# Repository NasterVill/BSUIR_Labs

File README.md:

# BSUIR (Belarusian State University of Informatics and Radioelectronics) laboratory works

## Intro
Here I've gathered most of the laboratory works from the CMSnN (Computing Machines, Systems and Networks) course which I've been working on. Some of the labs are far beyond redemption, but all the others are or will be here.

## Course Navigation

### 1 term

* [Algorithms and Programming Foundations](https://github.com/NasterVill/BSUIR_Labs/tree/master/1%20term/Algorithms-and-Programming-Foundations)

### 2 term

* [Algorithms and Programming Foundations](https://github.com/NasterVill/BSUIR_Labs/tree/master/2%20term/Algorithms-and-Programming-Foundations)
* [Arithmetic and Logic Basics of Computing Machines (Course Work)](https://github.com/NasterVill/BSUIR_Labs/tree/master/CourseWorks/Arithmetic-and-Logic-Basics-of-Computing-Machines)

### 3 term
* [Programming Design and Programming Languages (C++)](https://github.com/NasterVill/BSUIR_Labs/tree/master/3%20term/Programming-Design-and-Programming-Languages-C%2B%2B)
* [Lightning Paint (Course Work)](https://github.com/NasterVill/BSUIR_Labs/tree/master/CourseWorks/LightningPaint)
An application for drawing and simple image editing

### 4 term
* [System Software](https://github.com/NasterVill/BSUIR_Labs/tree/master/4%20term/System_Software_-SPO-)
* [Cross Platform Programming](https://github.com/NasterVill/BSUIR_Labs/tree/master/4%20term/Cross_Platform_Programming-Course)
* [Programming Design and Programming Languages (Assembly)](https://github.com/NasterVill/BSUIR_Labs/tree/master/4%20term/Programming-Design-and-Programming-Languages-Assembly)
* [Personal Computer Architecture](https://github.com/NasterVill/BSUIR_Labs/tree/master/4%20term/Personal-Computer-Architecture)
* [Lightning Tuner (Course Work)](https://github.com/NasterVill/BSUIR_Labs/tree/master/CourseWorks/LightningTuner)
An application for guitar tuning (written in Java) based of FFT algorithm

### 5 term

* [Interfaces and Peripheral Devices](https://github.com/NasterVill/BSUIR_Labs/tree/master/5%20term/Interfaces-and-Peripheral-Devices-IPD-)
* [Theoretical Foundations of Computer Networks](https://github.com/NasterVill/BSUIR_Labs/tree/master/5%20term/Theoretical-Foundations-of-Computer-Networks-TFoCN)
* [Structural and Functional Organization of Electronic Computing Machines](https://github.com/NasterVill/BSUIR_Labs/tree/master/5%20term/Structural-and-Functional-Organization-of-Electronic-%D0%A1omputing-Machines-SFOECM)
* [Circuit Design (Course Work)](https://github.com/NasterVill/BSUIR_Labs/tree/master/CourseWorks/Circuit-Design)

### 6 term

* [Digital Signal and Image Processing](https://github.com/NasterVill/BSUIR_Labs/tree/master/6%20term/DSIP-Digital-Signal-and-Image-Processing-)
* [System Analysis](https://github.com/NasterVill/BSUIR_Labs/tree/master/6%20term/SA%20(System-Analysis))
* [High Performance Processors Architecture](https://github.com/NasterVill/BSUIR_Labs/tree/master/6%20term/HPPA-High-Performance-Processors-Architecture)
* [Software Development and Testing Technologies](https://github.com/NasterVill/BSUIR_Labs/tree/master/6%20term/GoParty%20(Software-Development-and-Testing-Technologies))

### 7 term

* [Digital Signal and Image Processing](https://github.com/NasterVill/BSUIR_Labs/tree/master/7%20term/DSIP-Digital-Signal-and-Image-Processing)
* [Computer Aided Design of Computers and Systems](https://github.com/NasterVill/BSUIR_Labs/tree/master/7%20term/Computer-Aided-Design-of-Computers-and-Systems)
* [Local Computer Networks System Software](https://github.com/NasterVill/BSUIR_Labs/tree/master/7%20term/Local-Computer-Networks-System-Software)
* [Microprocessor Systems and Tools](https://github.com/NasterVill/BSUIR_Labs/tree/master/7%20term/Microprocessor-Systems-and-Tools)
* [Modeling](https://github.com/NasterVill/BSUIR_Labs/tree/master/7%20term/Modeling)

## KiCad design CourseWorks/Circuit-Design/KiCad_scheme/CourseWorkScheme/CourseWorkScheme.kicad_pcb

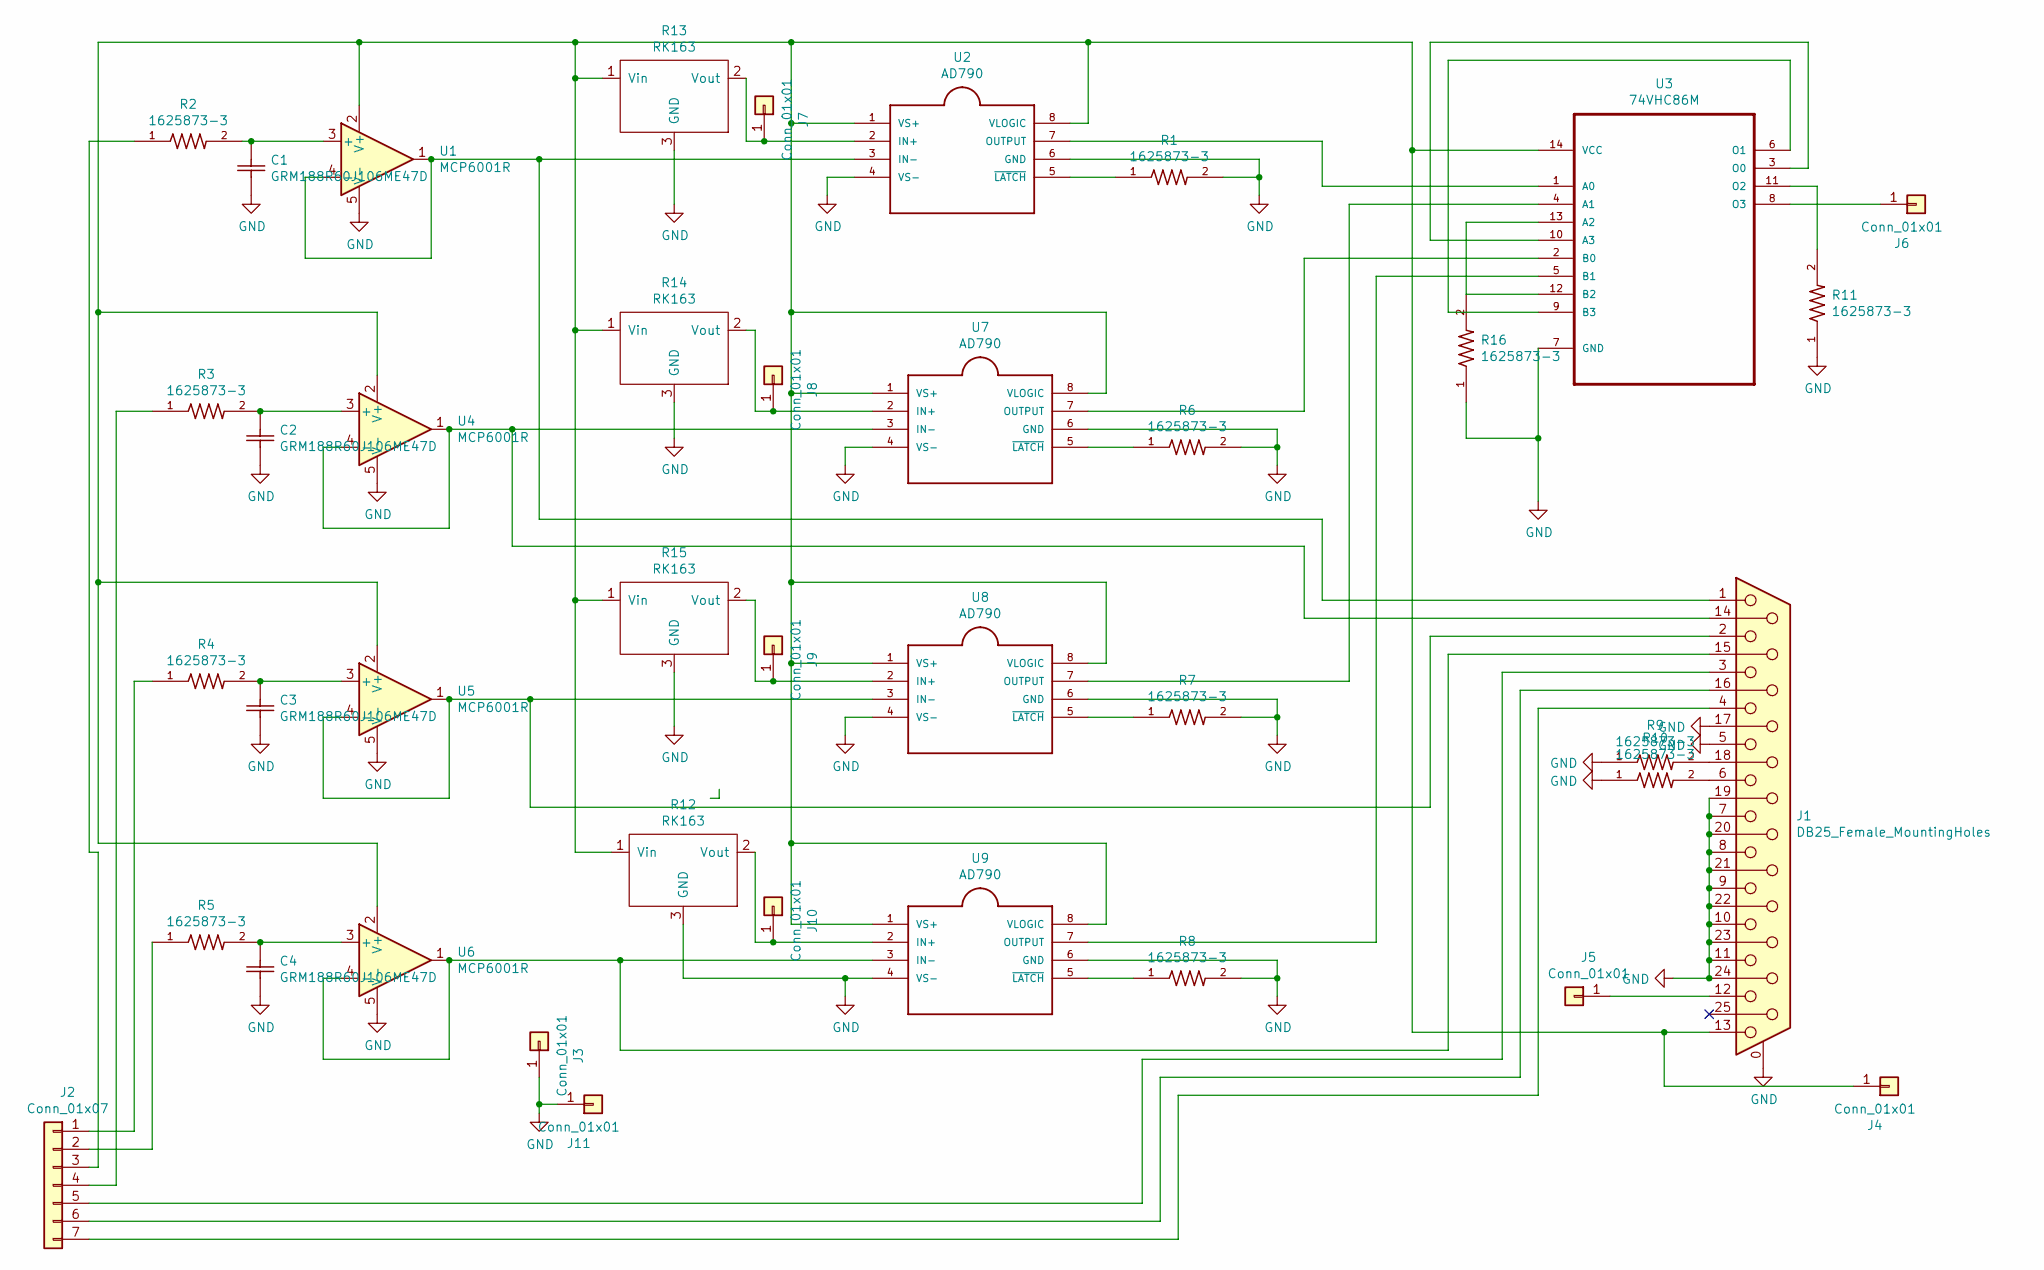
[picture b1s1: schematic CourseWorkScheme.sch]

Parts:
C1, C2, C3, C4: GRM188R60J106ME47D; CP_Radial_D5.0mm_P2.00mm
J1: DB25_Female_MountingHoles; DSUB-25_Female_Vertical_P2.77x2.84mm_MountingHoles
J2: Conn_01x07; PinSocket_1x07_P2.00mm_Vertical
J3, J7, J8, J9, J10: Conn_01x01; PinSocket_1x01_P2.00mm_Vertical
J4, J5, J6, J11: Conn_01x01; SolderWirePad_1x01_Drill1.5mm
R1, R2, R3, R4, R5, R6, R7, R8, R9, R10, R11, R16: 1625873-3; R_Axial_DIN0309_L9.0mm_D3.2mm_P15.24mm_Horizontal
R12, R13, R14, R15: RK163; Potentiometer_Alps_RK163_Single_Horizontal
U1, U4, U5, U6: MCP6001R; SOT-23-5
U2, U7, U8, U9: AD790; PDIP-8
U3: 74VHC86M; SOIC127P600X175-14N

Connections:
GND: C1.2 (C2), C2.2 (C2), C3.2 (C2), C4.2 (C2), J1.0 (PAD), J1.5, J1.7, J1.8, J1.9, J1.10, J1.11, J1.17, J1.19, J1.20, J1.21, J1.22, J1.23, J1.24, J3.1, J11.1, R1.2, R6.2, R7.2, R8.2, R9.1, R10.1, R11.1, R12.3 (GND), R13.3 (GND), R14.3 (GND), R15.3 (GND), R16.1, U1.5 (V-), U2.4 (VS-), U2.6 (GND), U3.7 (GND), U4.5 (V-), U5.5 (V-), U6.5 (V-), U7.4 (VS-), U7.6 (GND), U8.4 (VS-), U8.6 (GND), U9.4 (VS-), U9.6 (GND)
unnamed: C1.1 (C1), R2.2, U1.3 (+)
unnamed: C2.1 (C1), R3.2, U4.3 (+)
unnamed: C3.1 (C1), R4.2, U5.3 (+)
unnamed: C4.1 (C1), R5.2, U6.3 (+)
unnamed: J1.1, U1.1, U1.4 (-), U2.3 (IN-)
unnamed: J1.2, U5.1, U5.4 (-), U8.3 (IN-)
unnamed: J1.3, J2.5
unnamed: J1.4, J2.7
unnamed: J1.6, R10.2
unnamed: J1.12, J5.1
unnamed: J1.13, J4.1, R12.1 (Vin), R13.1 (Vin), R14.1 (Vin), R15.1 (Vin), U1.2 (V+), U2.1 (VS+), U2.8 (VLOGIC), U3.14 (VCC), U4.2 (V+), U5.2 (V+), U6.2 (V+), U7.1 (VS+), U7.8 (VLOGIC), U8.1 (VS+), U8.8 (VLOGIC), U9.1 (VS+), U9.8 (VLOGIC)
unnamed: J1.14, U4.1, U4.4 (-), U7.3 (IN-)
unnamed: J1.15, U6.1, U6.4 (-), U9.3 (IN-)
unnamed: J1.16, J2.6
unnamed: J1.18, R9.2
unnamed: J2.1, R4.1
unnamed: J2.2, R5.1
unnamed: J2.3, R2.1
unnamed: J2.4, R3.1
unnamed: J6.1, U3.8 (O3)
unnamed: J7.1, R13.2 (Vout), U2.2 (IN+)
unnamed: J8.1, R14.2 (Vout), U7.2 (IN+)
unnamed: J9.1, R15.2 (Vout), U8.2 (IN+)
unnamed: J10.1, R12.2 (Vout), U9.2 (IN+)
unnamed: R1.1, U2.5 (~LATCH~)
unnamed: R6.1, U7.5 (~LATCH~)
unnamed: R7.1, U8.5 (~LATCH~)
unnamed: R8.1, U9.5 (~LATCH~)
unnamed: R11.2, U3.11 (O2)
unnamed: R16.2, U3.12 (B2), U3.13 (A2)
unnamed: U2.7 (OUTPUT), U3.1 (A0)
unnamed: U3.2 (B0), U7.7 (OUTPUT)
unnamed: U3.4 (A1), U8.7 (OUTPUT)
unnamed: U3.5 (B1), U9.7 (OUTPUT)
unnamed: U3.6 (O1), U3.9 (B3)
unnamed: U3.3 (O0), U3.10 (A3)

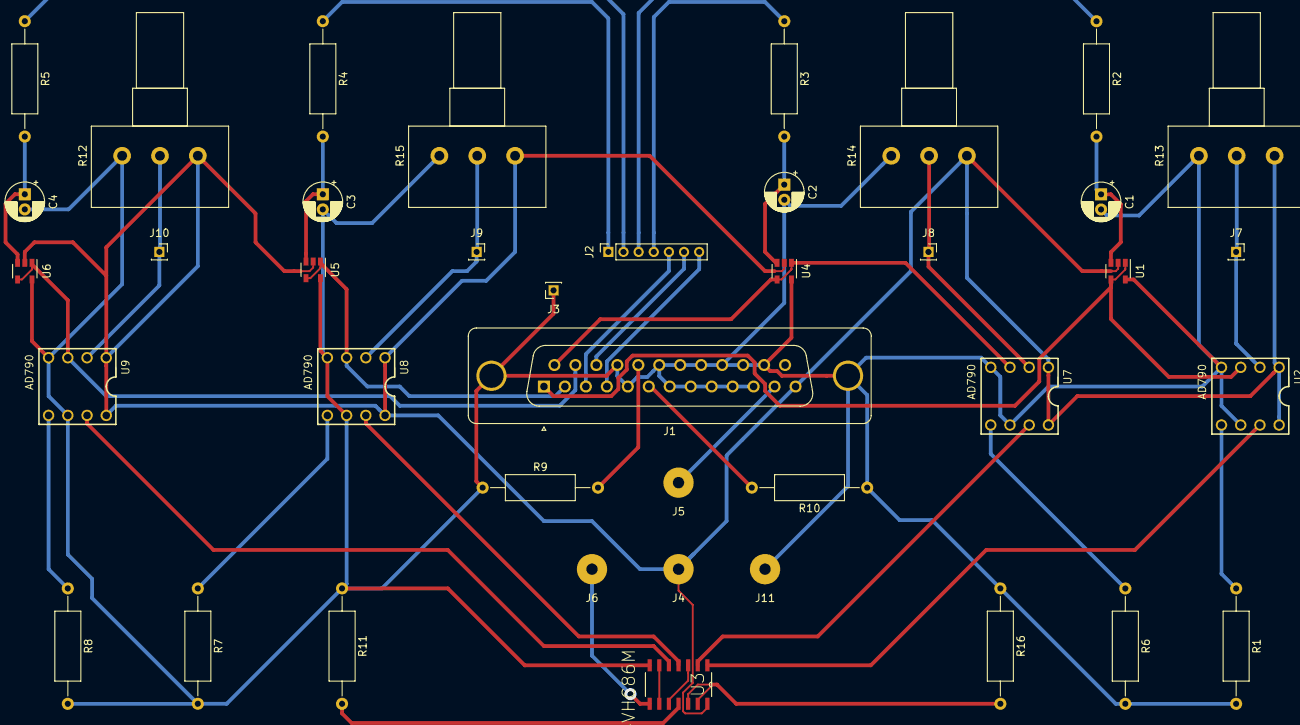
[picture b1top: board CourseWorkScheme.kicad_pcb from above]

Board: 2 copper layers, 40 parts (0 on the bottom side), 37 nets.

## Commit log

2019-05-23 Readme was added
2019-05-23 Grammar fix
2019-05-23 Readme refactoring
2019-05-23 Broken links were fixed
2019-05-24 Create LICENSE
2019-05-24 1, 2, 3 and 4 terms' labs were added (those which I've found)
2019-05-26 Readme was updated
2019-05-26 Encoding fix for 1 and 2 terms
2019-05-26 Minor changes
2019-05-27 Continue fixing the formats
2019-05-27 Folder refactoring
2019-05-27 Readme fix
2019-05-30 Refactoring for readme on PDnPL
2019-09-26 Labs 1-2 for DSIP and Modeling and lab 1 for CADoCaS
2019-09-29 Update for vhd and v handling in CADoCaS (АПВМиС)
2019-10-01 Lab 2 CADoCaS was added
2019-10-03 CADoCaS Lab 2 updated
2019-10-05 README update
2019-10-10 DSIP lab 3 implementation
2019-10-23 Lab 3 refactoring
2019-10-23 Lab 4 shape implementation
2019-10-23 Lab 4 implementation
2019-10-24 lcnss lab 1 flow refactoring
2019-10-24 LCNSS Lab 1 temp commit
2019-10-24 server message implementation for lcnss lab 1
2019-10-24 base command implementation
2019-10-24 server refactoring
2019-10-24 continue server refactoring
2019-10-24 upload implementation
2019-10-24 full base ECHO, TIME, CONNECT and DISCONNECT implementation
2019-10-24 client commands refactoring
2019-10-24 small fix for client commands
2019-10-24 base client configuration
2019-10-24 temp commit
2019-10-30 lcnss lab 1 implementation
2019-10-30 fix for client lcnss lab 1
2019-10-30 lcnss lab enhancements
2019-11-05 DSIP lab 5 implementation
2019-11-06 DSIP lab 5 fix
2019-11-06 CADoCaS lab 2 fix
2019-11-06 CADoCaS lab 3 temp
2019-11-06 CADoCaS lab 3 temp commit 2
2019-11-06 CADoCaS lab 3 temp commit 3
2019-11-06 CADoCaS lab 3 temp commit 4
2019-11-07 CADoCaS lab 3 final commit
2019-11-08 lcnss lab 1 fix for tcp keepalives
2019-11-08 lcnss lab 1 small refactoring
2019-11-08 Upload of old course works docs [term 3 - 5] and SFOECM(CиФОЭВМ)
2019-11-08 Small edit for Circuit Design course work
2019-11-09 MSaT labs 1 to 4 commit
2019-11-11 MSaT Lab 4 refactoring
2019-11-11 MSaT Lab 4 further refactoring
2019-11-11 MSaT Lab 4 further refactoring 2
2019-11-11 MSaT Lab 4 fix
2019-11-12 lab 4 msat refactoring
2019-11-13 lab 4 msat furhter refactoring
2019-11-13 lab 4 final refactoring
2019-11-16 MSaT lab 5 implementation
2019-11-21 CADoCAS lab 4 implementation
2019-11-21 DSIP lab 6 implementation (STare project analysis)
2019-11-26 lab 5 refactoring
2019-11-27 LCNSS lab 1 refactoring and lab 4 boilerplate
2019-11-27 LCNSS lab 4 base implementation
2019-11-27 LCNSS lab 4 refactoring
2019-11-27 LCNSS lab 2 implementation and cadocas pdf with tasks
2019-11-27 LCNSS lab 3 (tcp only) implementation
2019-11-28 LCNSS lab 2 and 4 fixes
2019-11-28 сlean up
2019-12-14 MSaT lab 6 implementation
